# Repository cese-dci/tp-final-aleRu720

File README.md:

## Trabajo práctico final de la asignatura DCI ##
Este repositorio contiene el trabajo práctico final para la asignatura de Diseño de Circuitos Impresos de la carrera de posgrado de FIUBA.

* Autor: Ing. Alejandro Rougier
* Título corto del trabajo:  Réplica AD8495 K-type thermocouple amplifier
* Descripción: 
Amplificador para termocupla tipo K, con salida analógica, basado en el amplificador de precisión para termocuplas, con compensación de unión fría AD8495 de Analog Device

## Licencia de este trabajo ##
Se utiliza la licencia CERN-OHL-P v2

## Estructura del TP FINAL ##

* doc: 
  * Notas de ingeniería propias.
  * Notas de aplicación propias.
  * Estudios previos, estado del arte, resumen de las investigaciones.
  * Notas con cálculos.
  * Dibujos adicionales.
  * Fotos de los prototipos.
  * Presupuestos, cotizaciones.
* info: 
  * Hojas de datos.
  * Notas de aplicación.
  * Info de productos comerciales.
  * Info en internet.
* pcb: Archivos de diseño esquemático y pcb.

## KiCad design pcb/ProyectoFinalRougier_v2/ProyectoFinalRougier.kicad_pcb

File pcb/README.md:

# Archivos Kicad #

## Contenido del Directorio:

El directorio contine 2 carpetas, **ProyectoFinalRougier_v1** y **ProyectoFinalRougier_v2**

Ambas carpetas continen en su interior los siguientes archivos:

* Archivos de proyecto.
* Esquemático.
* PCB.
* Modelos  3D( archivo.wrl).

Difieren entre sí en la disposición de los componentes en el PCB. Esto se hizo así porque el proyecto es una réplica de un amplificador de 
termocuplas de la firma ***ADAFRUIT***. 
El original, es para una sola termocupla, la réplica se pidió para dos termocuplas por lo que el circuito se duplicaba.

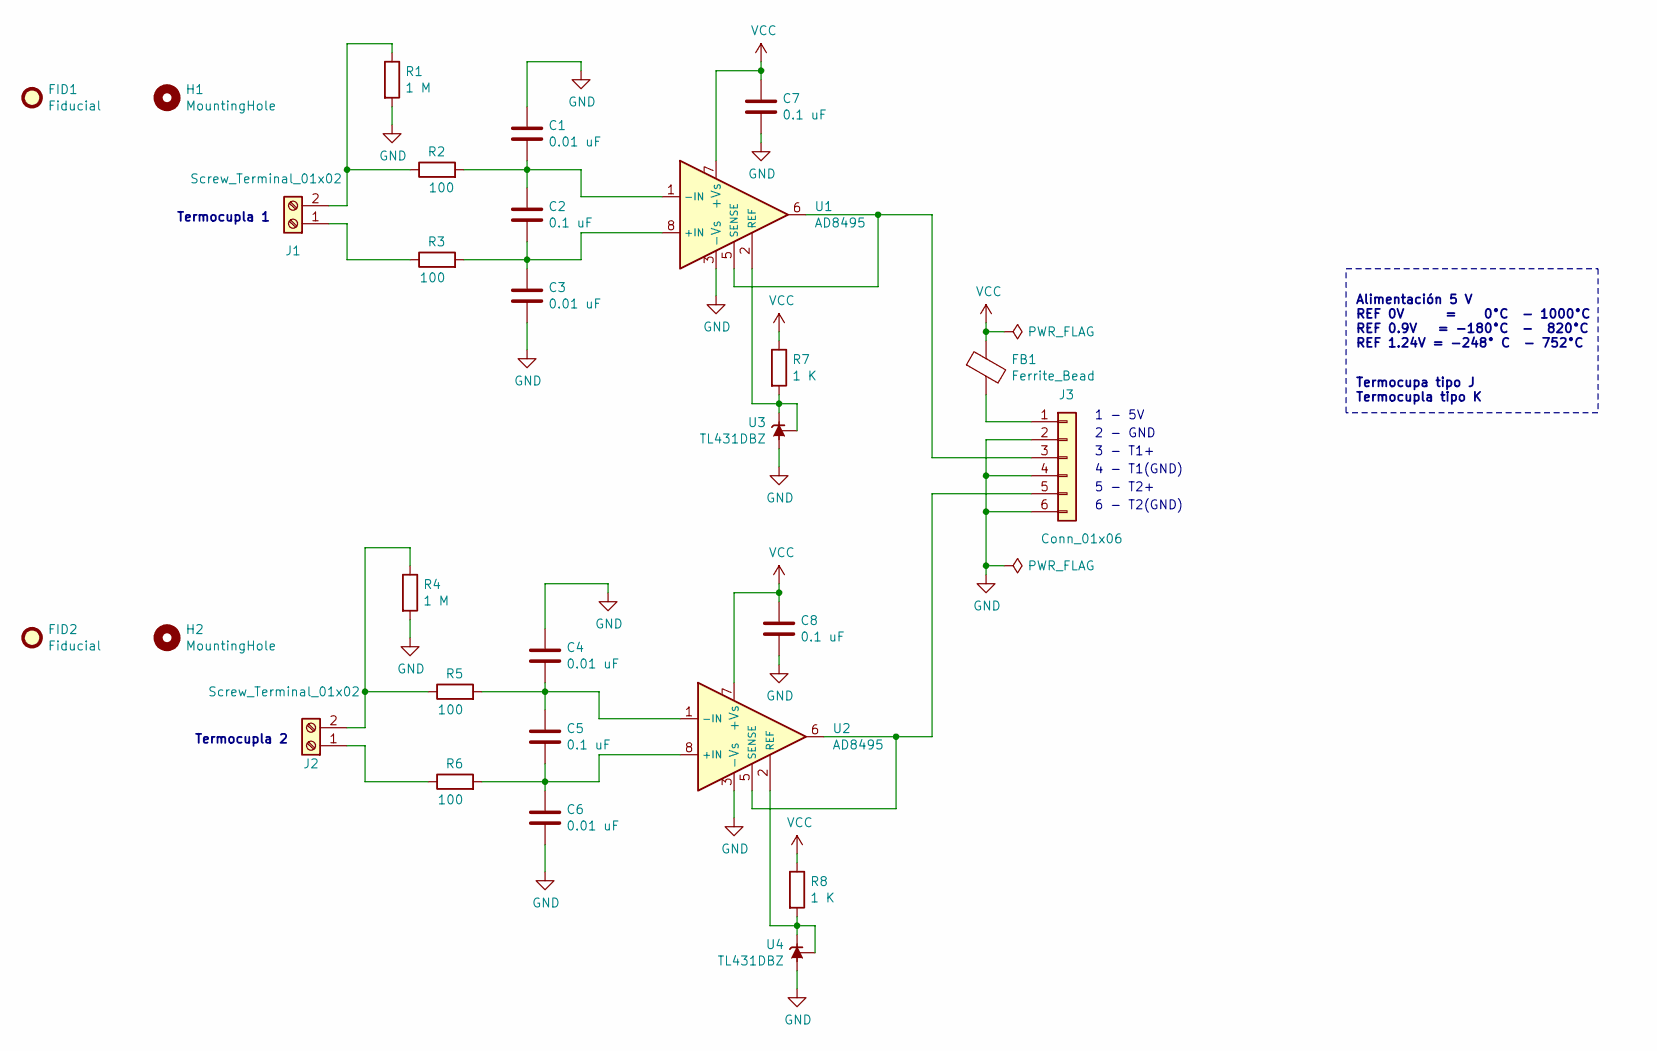
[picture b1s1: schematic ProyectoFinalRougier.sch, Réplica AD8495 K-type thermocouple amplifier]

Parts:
C1, C3, C4, C6: 0.01 uF; C_0805_2012Metric
C2, C5, C7, C8: 0.1 uF; C_0805_2012Metric
FB1: Ferrite_Bead; D_0805_2012Metric
FID1, FID2: Fiducial; Fiducial_0.75mm_Mask2.25mm
H1, H2: MountingHole; MountingHole_2.5mm
J1, J2: Screw_Terminal_01x02; TerminalBlock_Phoenix_PT-1,5-2-3.5-H_1x02_P3.50mm_Horizontal; Mouser Cod: 651-1888807
J3: Conn_01x06; PinHeader_1x06_P2.54mm_Vertical
R1, R4: 1 M; R_0805_2012Metric
R2, R3, R5, R6: 100; R_0805_2012Metric
R7, R8: 1 K; R_0805_2012Metric
U1, U2: AD8495; MSOP-8_3x3mm_P0.65mm; Mouser Cod: 584-AD8495ARMZ-R7
U3, U4: TL431DBZ; SOT-23; Mouser Cod: 595-TL431BIDBZR

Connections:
GND: C1.1, C3.2, C4.1, C6.2, C7.2, C8.2, J3.2, J3.4, J3.6, R1.2, R4.2, U1.3 (-Vs), U2.3 (-Vs), U3.3 (A), U4.3 (A)
unnamed: C1.2, C2.1, R2.2, U1.1 (-IN)
unnamed: C2.2, C3.1, R3.2, U1.8 (+IN)
unnamed: C4.2, C5.1, R5.2, U2.1 (-IN)
unnamed: C5.2, C6.1, R6.2, U2.8 (+IN)
unnamed: FB1.2, J3.1
unnamed: J1.1, R3.1
unnamed: J1.2, R1.1, R2.1
unnamed: J2.1, R6.1
unnamed: J2.2, R4.1, R5.1
unnamed: J3.3, U1.5 (SENSE), U1.6
unnamed: J3.5, U2.5 (SENSE), U2.6
unnamed: R7.2, U1.2 (REF), U3.1 (K), U3.2 (REF)
unnamed: R8.2, U2.2 (REF), U4.1 (K), U4.2 (REF)
VCC: C7.1, C8.1, FB1.1, R7.1, R8.1, U1.7 (+Vs), U2.7 (+Vs)

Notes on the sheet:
Termocupa tipo J Termocupla tipo K
Termocupla 2
Alimentación 5 V REF 0V = 0°C - 1000°C REF 0.9V = -180°C - 820°C REF 1.24V = -248° C - 752°C
Termocupla 1
1 - 5V
2 - GND
3 - T1+
4 - T1(GND)
5 - T2+
6 - T2(GND)

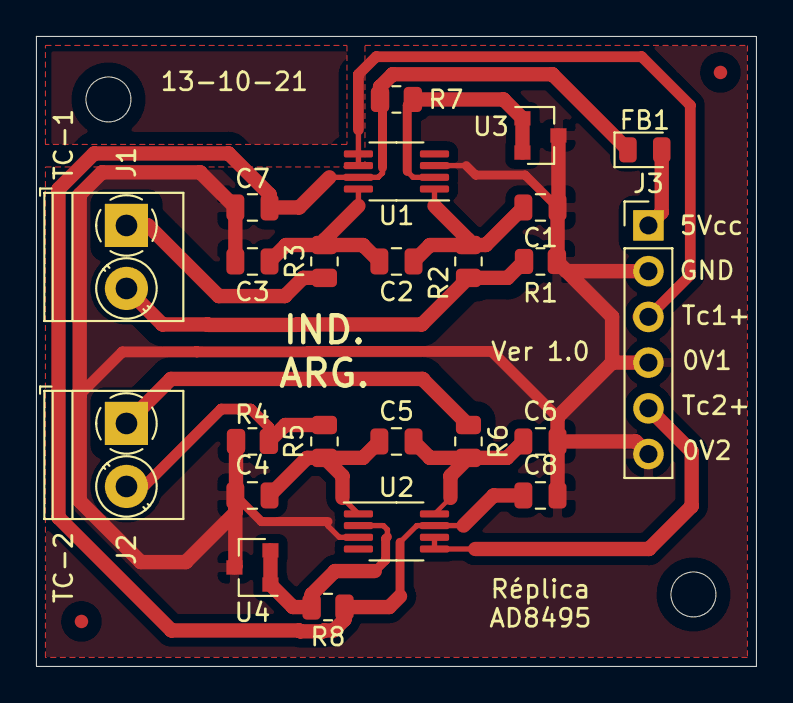
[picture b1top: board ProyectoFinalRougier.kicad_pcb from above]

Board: 2 copper layers, 40.0 x 35.0 mm, 28 parts (0 on the bottom side), 15 nets.

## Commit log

2021-09-14 Se agregan los archivos de la propuesta
2021-09-14 Se agrega la Licencia
2021-09-20 Se agrega el esquemático completo, con la asociación de huellas y los valores de componentes. Se ejecutó ECR y se corrigieron los warning
2021-09-22 Se agregan Fiduciales y Mounting hole, se corrige ubicación de algunos componentes
2021-10-07 Se agregan 2 carpetas con el mismo proyecto pero con distinta disposición del PCB.
2021-10-13 Se agregan comentarios adicionales al PCB
2021-10-13 Se agregan etiquetas y comentarios a los dos PCBs
2021-10-15 Ajuste del Margen, se aumentó el menor margen que limita el AD8495
